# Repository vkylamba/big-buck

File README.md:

# High Voltage Buck Converter with WiFi/Bluetooth Monitoring

This repository provides the hardware design and firmware/software for a high-voltage DC-DC buck converter. The converter efficiently steps down a high-voltage input (up to 600V DC) to 50V DC at a maximum power output of 1kW. The system includes WiFi and Bluetooth monitoring capabilities for real-time performance tracking and diagnostics.

---

## Table of Contents
- [Overview](#overview)
- [Features](#features)
- [Specifications](#specifications)
- [Hardware Design](#hardware-design)
- [Software & Firmware](#software--firmware)
- [Setup and Installation](#setup-and-installation)
- [Usage](#usage)
- [Contributing](#contributing)
- [License](#license)

---

## Overview

The high-voltage buck converter in this project is designed to operate in applications where high input voltages (up to 600V DC) must be efficiently converted to a lower, stable output voltage (50V DC) with a power output of up to 1kW. This system is ideal for industrial applications, renewable energy systems, and other high-power applications requiring reliable DC-DC conversion. The addition of WiFi and Bluetooth capabilities allows for remote monitoring, diagnostics, and control.

---

## Features

- **High Input Voltage:** Accepts up to 600V DC.
- **Stable Output Voltage:** Steps down to 50V DC with up to 1kW power output.
- **Efficient Conversion:** Designed for high efficiency across various loads.
- **Remote Monitoring:** WiFi and Bluetooth connectivity for real-time monitoring.
- **Compact Design:** Optimized layout for minimal footprint and high heat dissipation.
- **Safety Protections:** Includes overcurrent, overvoltage, and thermal protections.

---

## Specifications

| Parameter               | Value               |
|-------------------------|---------------------|
| Input Voltage Range     | 0 - 600V DC        |
| Output Voltage          | 50V DC             |
| Maximum Power Output    | 1kW                |
| Conversion Efficiency   | Up to 95%          |
| Communication Protocols | WiFi, Bluetooth    |
| Protections             | Overcurrent, Overvoltage, Over-temperature |

---

## Hardware Design

The hardware design files include the schematics, PCB layouts, and bill of materials (BOM). The design is modular and includes components for power management, filtering, and wireless communication. Files provided:

- **Schematics** (`/hardware/schematics`)
- **PCB Layouts** (`/hardware/pcb`)
- **Bill of Materials (BOM)** (`/hardware/bom`)

### Hardware Requirements

- **High-Voltage MOSFETs/IGBTs**
- **Inductors and Capacitors** for filtering
- **Microcontroller** with WiFi/Bluetooth support (e.g., ESP32)
- **Thermal Management**: Heat sinks and fans
- **Protective Components**: Fuses, TVS diodes

Refer to the hardware directory for more detailed information on components and assembly.

---

## Software & Firmware

This repository provides firmware for the microcontroller and a desktop/mobile application for monitoring.

- **Firmware** (`/software/firmware`): Code for controlling the buck converter, managing conversions, and handling wireless communications.
- **Monitoring App** (`/software/app`): Application for Windows, Linux, and mobile devices (Android/iOS) that connects to the converter via WiFi/Bluetooth.

### Key Software Features

- **Voltage & Current Monitoring**
- **Temperature Monitoring**
- **Fault Detection**
- **Remote On/Off Control**
- **Firmware Updates Over-the-Air (OTA)**

---

## Setup and Installation

### Hardware Setup

1. Assemble the hardware components as per the schematic and PCB layout.
2. Verify connections and ensure all safety precautions are followed, especially for high-voltage testing.
3. Connect the microcontroller to the buck converter control circuitry.

### Firmware Installation

1. Clone this repository:
   ```bash
   git clone https://github.com/vkylamba/big-buck.git
   cd big-buck/software/firmware
2. Compile and upload the firmware to the microcontroller using your preferred IDE (e.g., Arduino IDE, PlatformIO).
3. Set up WiFi and Bluetooth configurations in the firmware for monitoring.

### Monitoring App Installation
Instructions for installing the monitoring application on desktop and mobile devices are in the software/app directory.

### Usage
Power On: Supply high-voltage input to the converter.
Monitor: Connect to the buck converter using the monitoring app via WiFi or Bluetooth.
Diagnostics and Control: View real-time voltage, current, and temperature. Turn the converter on/off and perform diagnostics if needed.

### Contributing
We welcome contributions from the community. Here’s how you can help:

Report Issues: Found a bug or have an enhancement request? Please open an issue in the GitHub repository.
Submit Pull Requests: Fork this repository, make changes, and submit a pull request. Be sure to follow coding standards and include comments where necessary.
Documentation: Help us improve this documentation by suggesting edits or additions.

### License
This project is licensed under the MIT License. See the LICENSE file for more information.

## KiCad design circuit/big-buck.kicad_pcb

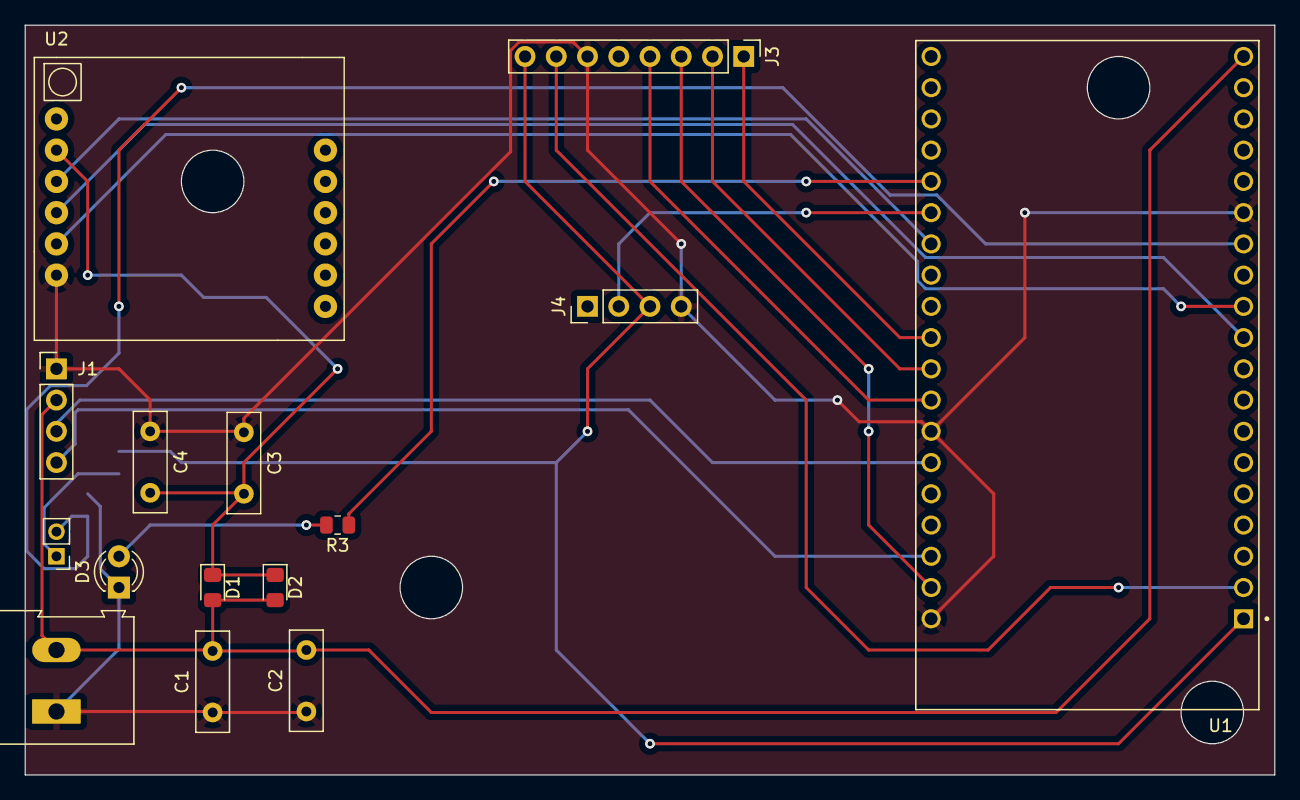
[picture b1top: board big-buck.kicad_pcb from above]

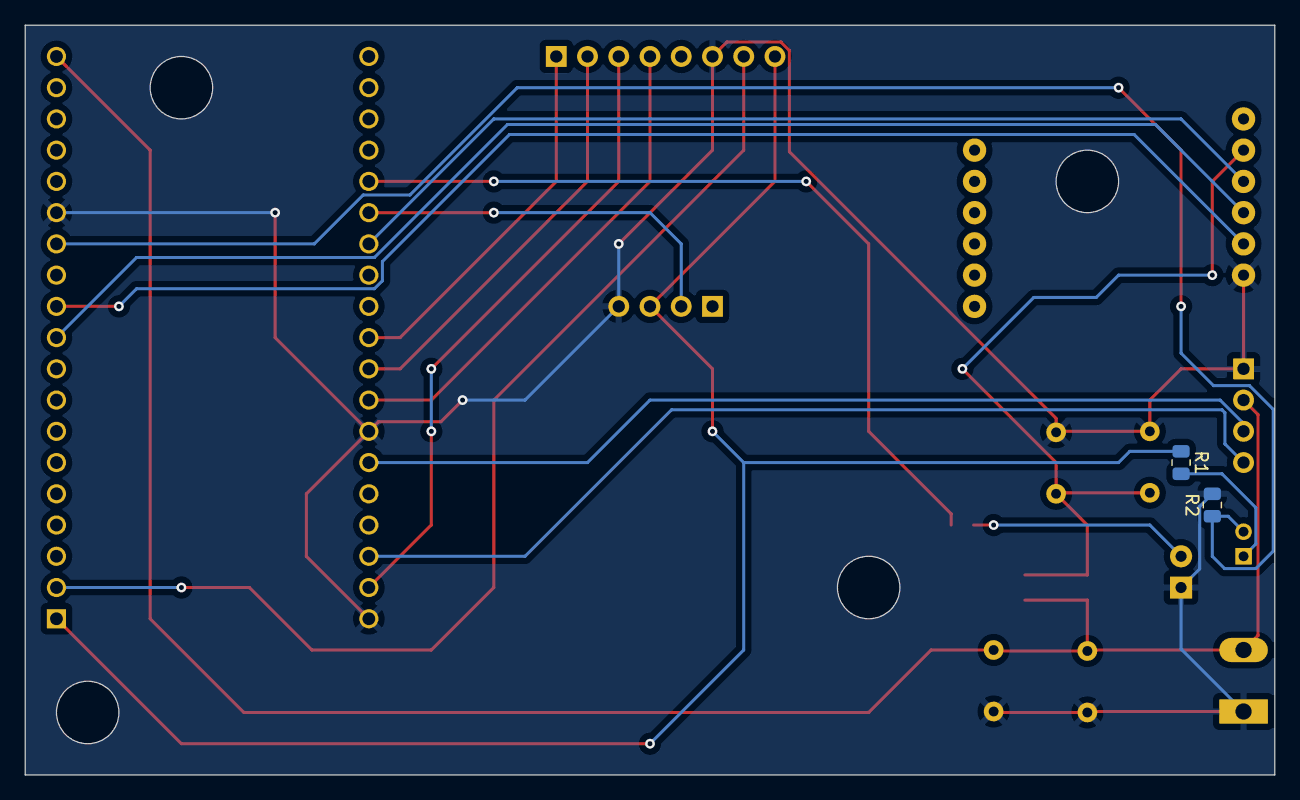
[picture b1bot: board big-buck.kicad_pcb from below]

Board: 2 copper layers, 101.6 x 61.0 mm, 17 parts (2 on the bottom side), 19 nets.

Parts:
C1, C2: 1000uF; C_Disc_D8.0mm_W2.5mm_P5.00mm
C3, C4: 470uF; C_Disc_D8.0mm_W2.5mm_P5.00mm
CFG1: CFG; PinHeader_1x02_P2.00mm_Vertical
D1, D2: 1N4007, SS14; D_0805_2012Metric_Pad1.15x1.40mm_HandSolder
D3: LED; LED_D3.0mm_FlatTop
J1: LCD; PinHeader_1x04_P2.54mm_Vertical
J3: SPI Etx; PinHeader_1x08_P2.54mm_Vertical
J4: Buzzer; PinHeader_1x04_P2.54mm_Vertical
J5: Power in; TerminalBlock_Altech_AK300-2_P5.00mm
R1: 50k; R_0805_2012Metric
R2: 100k; R_0805_2012Metric
R3: 1k; R_0805_2012Metric
U1: ESP32-DEVKITC-32D; MODULE_ESP32-DEVKITC-32D
U2: SIM800L-CORE

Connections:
+3V3: J3.8, J4.3, R1.1, U1.J2-1 (3V3)
+4V3: C3.2, C4.2, D1.1 (K), D2.1 (K), U2.2 (VCC)
+5V: C1.2, C2.2, D1.2 (A), D2.2 (A), J1.2, J5.2, U1.J2-19 (EXT_5V)
BUZZ: J4.2, U1.J3-14 (IO0)
CFG-BTN: CFG1.2, R2.1, U1.J2-13 (IO12)
EN: J3.7, U1.J2-2 (EN)
GND: C1.1, C2.1, C3.1, C4.1, D3.1 (K), J1.1, J3.6, J4.4, J5.1, R2.2, U1.J2-14 (GND1), U1.J3-1 (GND3), U1.J3-7 (GND2), U2.6 (GND)
GSM-RST: U1.J3-13 (IO4), U2.3 (RST)
GSM-RX: U1.J2-10 (IO26), U2.4 (RXD)
GSM-TX: U1.J2-11 (IO27), U2.5 (TXD)
LCD-SCL: J1.4, U1.J3-3 (IO22)
LCD-SDA: J1.3, U1.J3-6 (IO21)
LED: R3.1, U1.J3-15 (IO2)
unnamed: CFG1.1, R1.2
unnamed: D3.2 (A), R3.2
SD-CS-1: J3.1, U1.J3-10 (IO5)
SD-MISO: J3.4, U1.J3-8 (IO19)
SD-MOSI: J3.3, U1.J3-2 (IO23)
SD-SCK: J3.2, U1.J3-9 (IO18)
